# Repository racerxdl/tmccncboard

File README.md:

# tmccncboard

TMC2209 GRBL-ESP32 CNC Board

Made with Kicad 6.0

# FluidNC Configuration

This is the current profile I'm using for [FluidNC](https://github.com/bdring/FluidNC). Its currently WIP and should be used with care.

```yaml
board: Teske's Lab TMC CNC
name: TMCCNC
stepping:
  engine: RMT
  idle_ms: 255
  pulse_us: 2
  dir_delay_us: 1
  disable_delay_us: 0

axes:
  shared_stepper_disable_pin: gpio.27
  x:
    steps_per_mm: 1600.000
    max_rate_mm_per_min: 5000.000
    acceleration_mm_per_sec2: 100.000
    max_travel_mm: 250.000
    soft_limits: false
    homing:
      cycle: 2
      positive_direction: false
      mpos_mm: 150.000
      feed_mm_per_min: 100.000
      seek_mm_per_min: 200.000
      settle_ms: 500
      seek_scaler: 1.100
      feed_scaler: 1.100

    motor0:
      limit_neg_pin: NO_PIN
      limit_pos_pin: NO_PIN
      limit_all_pin: gpio.36
      hard_limits: false
      pulloff_mm:1.000

      tmc_2209:
        uart:
          txd_pin: gpio.17
          rxd_pin: gpio.16
        run_mode: StealthChop
        homing_mode: StallGuard
        step_pin: gpio.2
        direction_pin: gpio.4
        addr: 0
        r_sense_ohms: 0.110
        run_amps: 1.000
        hold_amps: 0.500
        microsteps: 16
  y:
    steps_per_mm: 400.000
    max_rate_mm_per_min: 5000.000
    acceleration_mm_per_sec2: 100.000
    max_travel_mm: 490.000
    soft_limits: false
    homing:
      cycle: 2
      positive_direction: true
      mpos_mm: 150.000
      feed_mm_per_min: 100.000
      seek_mm_per_min: 200.000
      settle_ms: 500
      seek_scaler: 1.100
      feed_scaler: 1.100

    motor0:
      limit_neg_pin: NO_PIN
      limit_pos_pin: NO_PIN
      limit_all_pin: gpio.39
      hard_limits: false
      pulloff_mm:1.000

      tmc_2209:
        run_mode: StealthChop
        homing_mode: StallGuard
        step_pin: gpio.12
        direction_pin: gpio.14
        addr: 1
        r_sense_ohms: 0.110
        run_amps: 1.000
        hold_amps: 0.500
        microsteps: 16

    motor1:
      limit_neg_pin: NO_PIN
      limit_pos_pin: NO_PIN
      limit_all_pin: gpio.34
      hard_limits: false
      pulloff_mm: 1.000
      tmc_2209:
        run_mode: StealthChop
        homing_mode: StallGuard
        step_pin: gpio.33
        direction_pin: gpio.32
        addr: 3
        r_sense_ohms: 0.110
        run_amps: 1.000
        hold_amps: 0.500
        microsteps: 16

  z:
    steps_per_mm: 400.000
    max_rate_mm_per_min: 5000.000
    acceleration_mm_per_sec2: 100.000
    max_travel_mm: 100.000
    soft_limits: false
    homing:
      cycle: 1
      positive_direction: true
      mpos_mm: 150.000
      feed_mm_per_min: 100.000
      seek_mm_per_min: 800.000
      settle_ms: 500
      seek_scaler: 1.100
      feed_scaler: 1.100

    motor0:
      limit_neg_pin: NO_PIN
      limit_pos_pin: NO_PIN
      limit_all_pin: gpio.35
      hard_limits: false
      pulloff_mm:1.000

      tmc_2209:
        run_mode: StealthChop
        homing_mode: StallGuard
        step_pin: gpio.26
        direction_pin: gpio.25
        addr: 2
        r_sense_ohms: 0.110
        run_amps: 1.000
        hold_amps: 0.500
        microsteps: 16

spi:
  miso_pin: gpio.19
  mosi_pin: gpio.23
  sck_pin: gpio.18

sdcard:
  cs_pin: gpio.5
  card_detect_pin: NO_PIN

probe:
  pin: NO_PIN
  check_mode_start: true

start:
  must_home: false

PWM:
  pwm_hz: 5000
  output_pin: gpio.13
  enable_pin: NO_PIN
  direction_pin: NO_PIN
  disable_with_s0: false
  s0_with_disable: true
  spinup_ms: 1000
  spindown_ms: 1000
  tool_num: 0
  speed_map: 0=0.000% 1000=100.000%

```

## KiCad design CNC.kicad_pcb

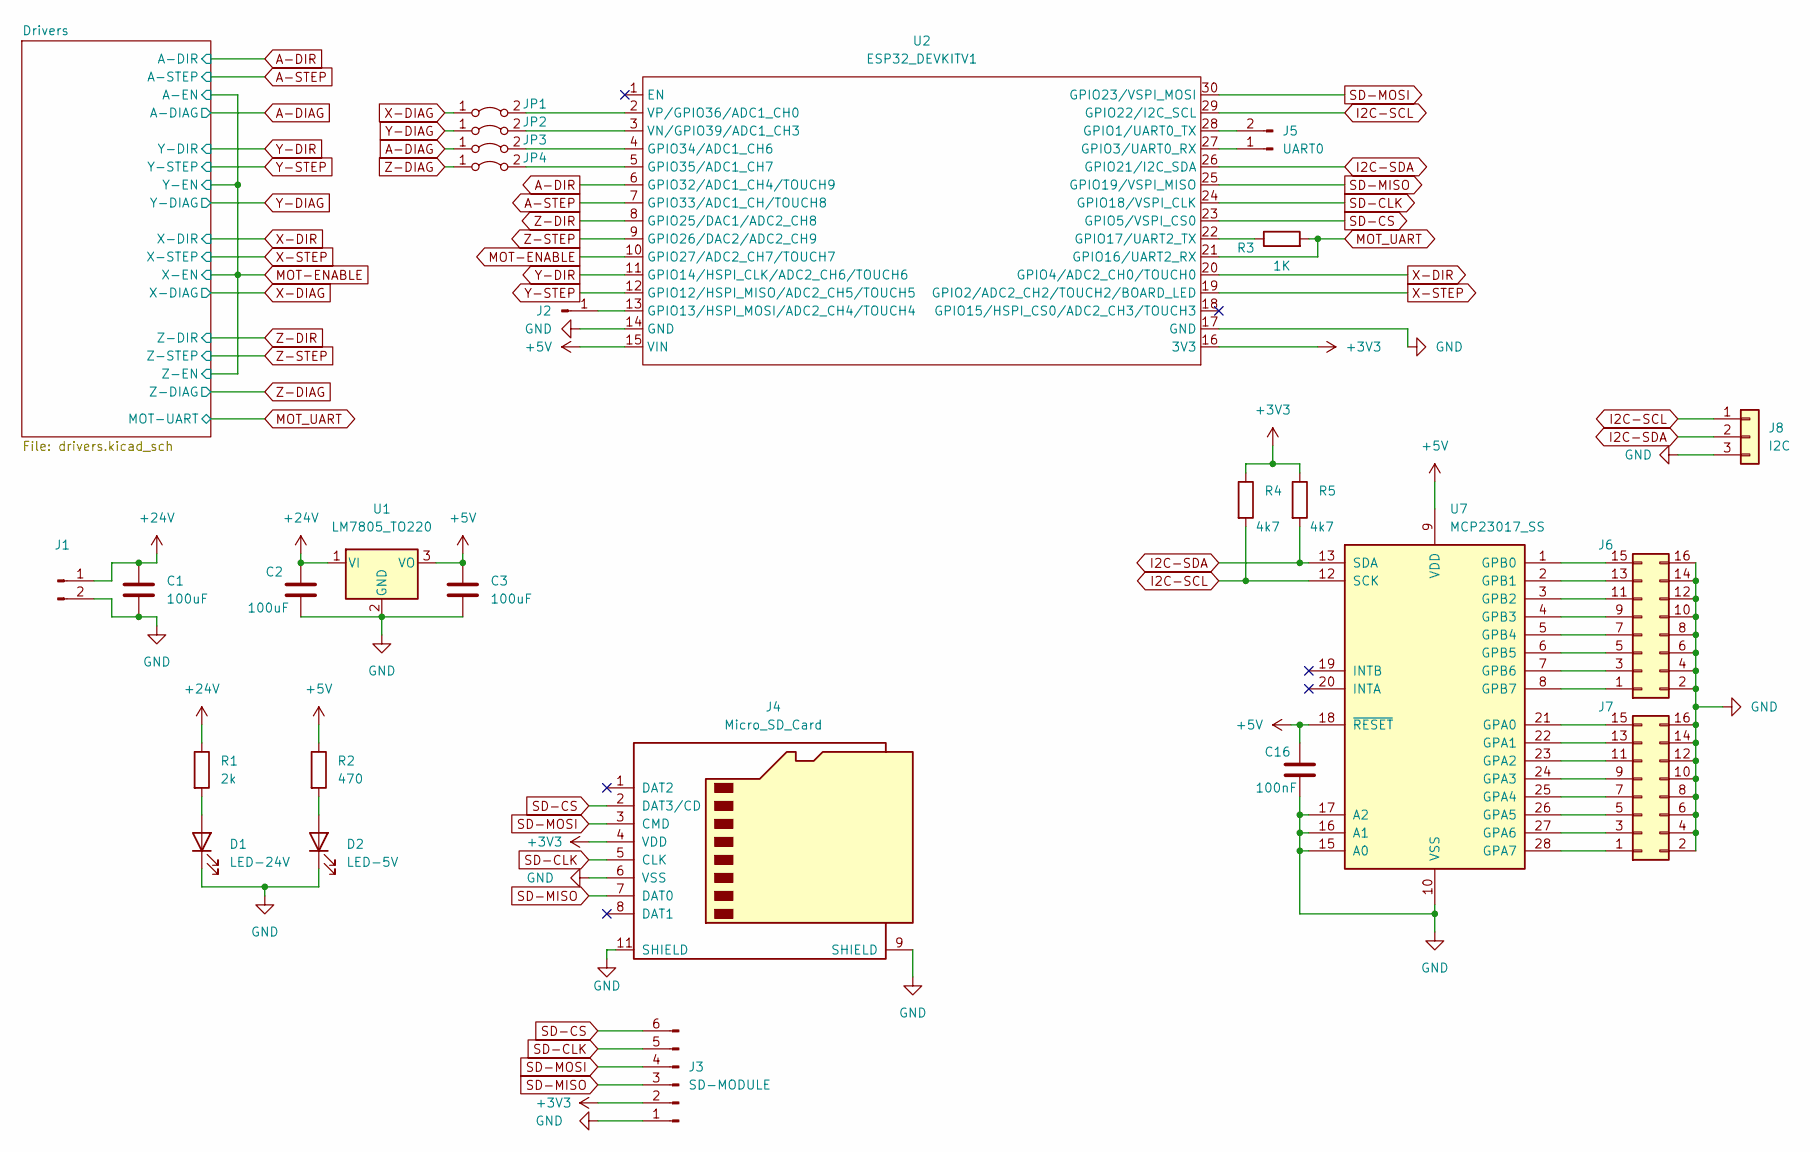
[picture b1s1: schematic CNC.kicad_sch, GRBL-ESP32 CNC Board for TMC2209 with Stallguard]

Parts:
C1, C2, C3: 100uF; CP_Radial_D8.0mm_P3.50mm
C16: 100nF; C_0805_2012Metric_Pad1.18x1.45mm_HandSolder
D1: LED-24V; LED_D5.0mm
D2: LED-5V; LED_D5.0mm
J1: Conn_01x02_Male; Altech_AK300_1x02_P5.00mm_45-Degree
J2: Conn_01x01_Male; PinHeader_1x01_P2.54mm_Vertical
J3: SD-MODULE; PinHeader_1x06_P2.54mm_Horizontal
J4: Micro_SD_Card; microSD_HC_Hirose_DM3AT-SF-PEJM5
J5: UART0; PinHeader_1x02_P2.54mm_Vertical
J6, J7: Conn_02x08_Odd_Even; IDC-Header_2x08_P2.54mm_Vertical
J8: I2C; FanPinHeader_1x03_P2.54mm_Vertical
JP1, JP2, JP3, JP4: Jumper_2_Bridged; PinHeader_1x02_P2.54mm_Vertical
R1: 2k; R_0805_2012Metric_Pad1.20x1.40mm_HandSolder
R2: 470; R_0805_2012Metric_Pad1.20x1.40mm_HandSolder
R3: 1K; R_0805_2012Metric_Pad1.20x1.40mm_HandSolder
R4, R5: 4k7; R_0805_2012Metric_Pad1.20x1.40mm_HandSolder
U1: LM7805_TO220; TO-220-3_Vertical
U2: ESP32_DEVKITV1; ESP32 DEVKITV1
U7: MCP23017_SS; SSOP-28_5.3x10.2mm_P0.65mm

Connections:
+3V3: J3.2, J4.4 (VDD), R4.1, R5.1, U2.16 (3V3); also elsewhere on the board
+5V: C3.1, C16.1, R2.1, U1.3 (VO), U2.15 (VIN), U7.9 (VDD), U7.18 (~RESET)
+24V: C1.1, C2.1, J1.1, R1.1, U1.1 (VI); also elsewhere on the board
A-DIAG: JP3.1 (A); also elsewhere on the board
A-DIR: U2.6 (GPIO32/ADC1_CH4/TOUCH9); also elsewhere on the board
A-STEP: U2.7 (GPIO33/ADC1_CH/TOUCH8); also elsewhere on the board
GND: C1.2, C2.2, C3.2, C16.2, D1.1 (K), D2.1 (K), J1.2, J3.1, J4.6 (VSS), J4.9 (SHIELD), J4.11 (SHIELD), J6.2, J6.4, J6.6, J6.8, J6.10, J6.12, J6.14, J6.16, J7.2, J7.4, J7.6, J7.8, J7.10, J7.12, J7.14, J7.16, J8.3, U1.2 (GND), U2.14 (GND), U2.17 (GND), U7.10 (VSS), U7.15 (A0), U7.16 (A1), U7.17 (A2); also elsewhere on the board
I2C-SCL: J8.1, R4.2, U2.29 (GPIO22/I2C_SCL), U7.12 (SCK)
I2C-SDA: J8.2, R5.2, U2.26 (GPIO21/I2C_SDA), U7.13 (SDA)
MOT-ENABLE: U2.10 (GPIO27/ADC2_CH7/TOUCH7); also elsewhere on the board
MOT_UART: R3.2, U2.21 (GPIO16/UART2_RX); also elsewhere on the board
unnamed: D1.2 (A), R1.2
unnamed: D2.2 (A), R2.2
unnamed: J2.1, U2.13 (GPIO13/HSPI_MOSI/ADC2_CH4/TOUCH4)
unnamed: J5.1, U2.27 (GPIO3/UART0_RX)
unnamed: J5.2, U2.28 (GPIO1/UART0_TX)
unnamed: J6.1, U7.8 (GPB7)
unnamed: J6.3, U7.7 (GPB6)
unnamed: J6.5, U7.6 (GPB5)
unnamed: J6.7, U7.5 (GPB4)
unnamed: J6.9, U7.4 (GPB3)
unnamed: J6.11, U7.3 (GPB2)
unnamed: J6.13, U7.2 (GPB1)
unnamed: J6.15, U7.1 (GPB0)
unnamed: J7.1, U7.28 (GPA7)
unnamed: J7.3, U7.27 (GPA6)
unnamed: J7.5, U7.26 (GPA5)
unnamed: J7.7, U7.25 (GPA4)
unnamed: J7.9, U7.24 (GPA3)
unnamed: J7.11, U7.23 (GPA2)
unnamed: J7.13, U7.22 (GPA1)
unnamed: J7.15, U7.21 (GPA0)
unnamed: JP1.2 (B), U2.2 (VP/GPIO36/ADC1_CH0)
unnamed: JP2.2 (B), U2.3 (VN/GPIO39/ADC1_CH3)
unnamed: JP3.2 (B), U2.4 (GPIO34/ADC1_CH6)
unnamed: JP4.2 (B), U2.5 (GPIO35/ADC1_CH7)
unnamed: R3.1, U2.22 (GPIO17/UART2_TX)
SD-CLK: J3.5, J4.5 (CLK), U2.24 (GPIO18/VSPI_CLK)
SD-CS: J3.6, J4.2 (DAT3/CD), U2.23 (GPIO5/VSPI_CS0)
SD-MISO: J3.3, J4.7 (DAT0), U2.25 (GPIO19/VSPI_MISO)
SD-MOSI: J3.4, J4.3 (CMD), U2.30 (GPIO23/VSPI_MOSI)
X-DIAG: JP1.1 (A); also elsewhere on the board
X-DIR: U2.20 (GPIO4/ADC2_CH0/TOUCH0); also elsewhere on the board
X-STEP: U2.19 (GPIO2/ADC2_CH2/TOUCH2/BOARD_LED); also elsewhere on the board
Y-DIAG: JP2.1 (A); also elsewhere on the board
Y-DIR: U2.11 (GPIO14/HSPI_CLK/ADC2_CH6/TOUCH6); also elsewhere on the board
Y-STEP: U2.12 (GPIO12/HSPI_MISO/ADC2_CH5/TOUCH5); also elsewhere on the board
Z-DIAG: JP4.1 (A); also elsewhere on the board
Z-DIR: U2.8 (GPIO25/DAC1/ADC2_CH8); also elsewhere on the board
Z-STEP: U2.9 (GPIO26/DAC2/ADC2_CH9); also elsewhere on the board

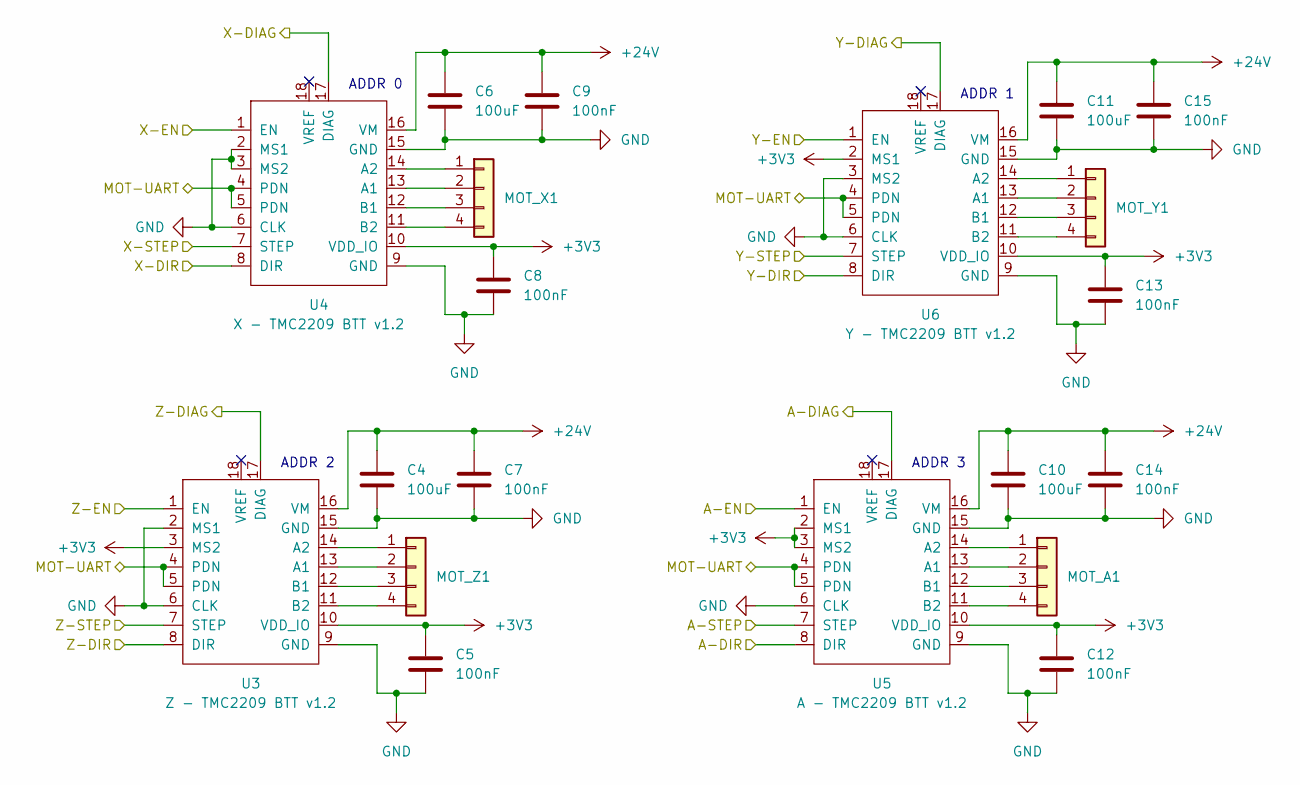
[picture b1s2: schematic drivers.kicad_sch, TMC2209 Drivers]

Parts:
C4, C6, C10, C11: 100uF; CP_Radial_D8.0mm_P3.50mm
C5, C7, C8, C9, C12, C13, C14, C15: 100nF; C_0805_2012Metric_Pad1.18x1.45mm_HandSolder
MOT_A1: Conn_01x04; PinHeader_1x04_P2.54mm_Vertical
MOT_X1: Conn_01x04; PinHeader_1x04_P2.54mm_Vertical
MOT_Y1: Conn_01x04; PinHeader_1x04_P2.54mm_Vertical
MOT_Z1: Conn_01x04; PinHeader_1x04_P2.54mm_Vertical
U3: Z - TMC2209 BTT v1.2; BTT-TMC2209
U4: X - TMC2209 BTT v1.2; BTT-TMC2209
U5: A - TMC2209 BTT v1.2; BTT-TMC2209
U6: Y - TMC2209 BTT v1.2; BTT-TMC2209

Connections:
+3V3: C5.1, C8.1, C12.1, C13.1, U3.3 (MS2), U3.10 (VDD_IO), U4.10 (VDD_IO), U5.2 (MS1), U5.3 (MS2), U5.10 (VDD_IO), U6.2 (MS1), U6.10 (VDD_IO); also elsewhere on the board
+24V: C4.1, C6.1, C7.1, C9.1, C10.1, C11.1, C14.1, C15.1, U3.16 (VM), U4.16 (VM), U5.16 (VM), U6.16 (VM); also elsewhere on the board
A-DIAG: U5.17 (DIAG); also elsewhere on the board
A-DIR: U5.8 (DIR); also elsewhere on the board
A-STEP: U5.7 (STEP); also elsewhere on the board
GND: C4.2, C5.2, C6.2, C7.2, C8.2, C9.2, C10.2, C11.2, C12.2, C13.2, C14.2, C15.2, U3.2 (MS1), U3.6 (CLK), U3.9 (GND), U3.15 (GND), U4.2 (MS1), U4.3 (MS2), U4.6 (CLK), U4.9 (GND), U4.15 (GND), U5.6 (CLK), U5.9 (GND), U5.15 (GND), U6.3 (MS2), U6.6 (CLK), U6.9 (GND), U6.15 (GND); also elsewhere on the board
MOT-ENABLE: U3.1 (EN), U4.1 (EN), U5.1 (EN), U6.1 (EN); also elsewhere on the board
MOT_UART: U3.4 (PDN), U3.5 (PDN), U4.4 (PDN), U4.5 (PDN), U5.4 (PDN), U5.5 (PDN), U6.4 (PDN), U6.5 (PDN); also elsewhere on the board
unnamed: MOT_A1.1, U5.14 (A2)
unnamed: MOT_A1.2, U5.13 (A1)
unnamed: MOT_A1.3, U5.12 (B1)
unnamed: MOT_A1.4, U5.11 (B2)
unnamed: MOT_X1.1, U4.14 (A2)
unnamed: MOT_X1.2, U4.13 (A1)
unnamed: MOT_X1.3, U4.12 (B1)
unnamed: MOT_X1.4, U4.11 (B2)
unnamed: MOT_Y1.1, U6.14 (A2)
unnamed: MOT_Y1.2, U6.13 (A1)
unnamed: MOT_Y1.3, U6.12 (B1)
unnamed: MOT_Y1.4, U6.11 (B2)
unnamed: MOT_Z1.1, U3.14 (A2)
unnamed: MOT_Z1.2, U3.13 (A1)
unnamed: MOT_Z1.3, U3.12 (B1)
unnamed: MOT_Z1.4, U3.11 (B2)
X-DIAG: U4.17 (DIAG); also elsewhere on the board
X-DIR: U4.8 (DIR); also elsewhere on the board
X-STEP: U4.7 (STEP); also elsewhere on the board
Y-DIAG: U6.17 (DIAG); also elsewhere on the board
Y-DIR: U6.8 (DIR); also elsewhere on the board
Y-STEP: U6.7 (STEP); also elsewhere on the board
Z-DIAG: U3.17 (DIAG); also elsewhere on the board
Z-DIR: U3.8 (DIR); also elsewhere on the board
Z-STEP: U3.7 (STEP); also elsewhere on the board

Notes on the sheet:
ADDR 2
ADDR 1
ADDR 3
ADDR 0

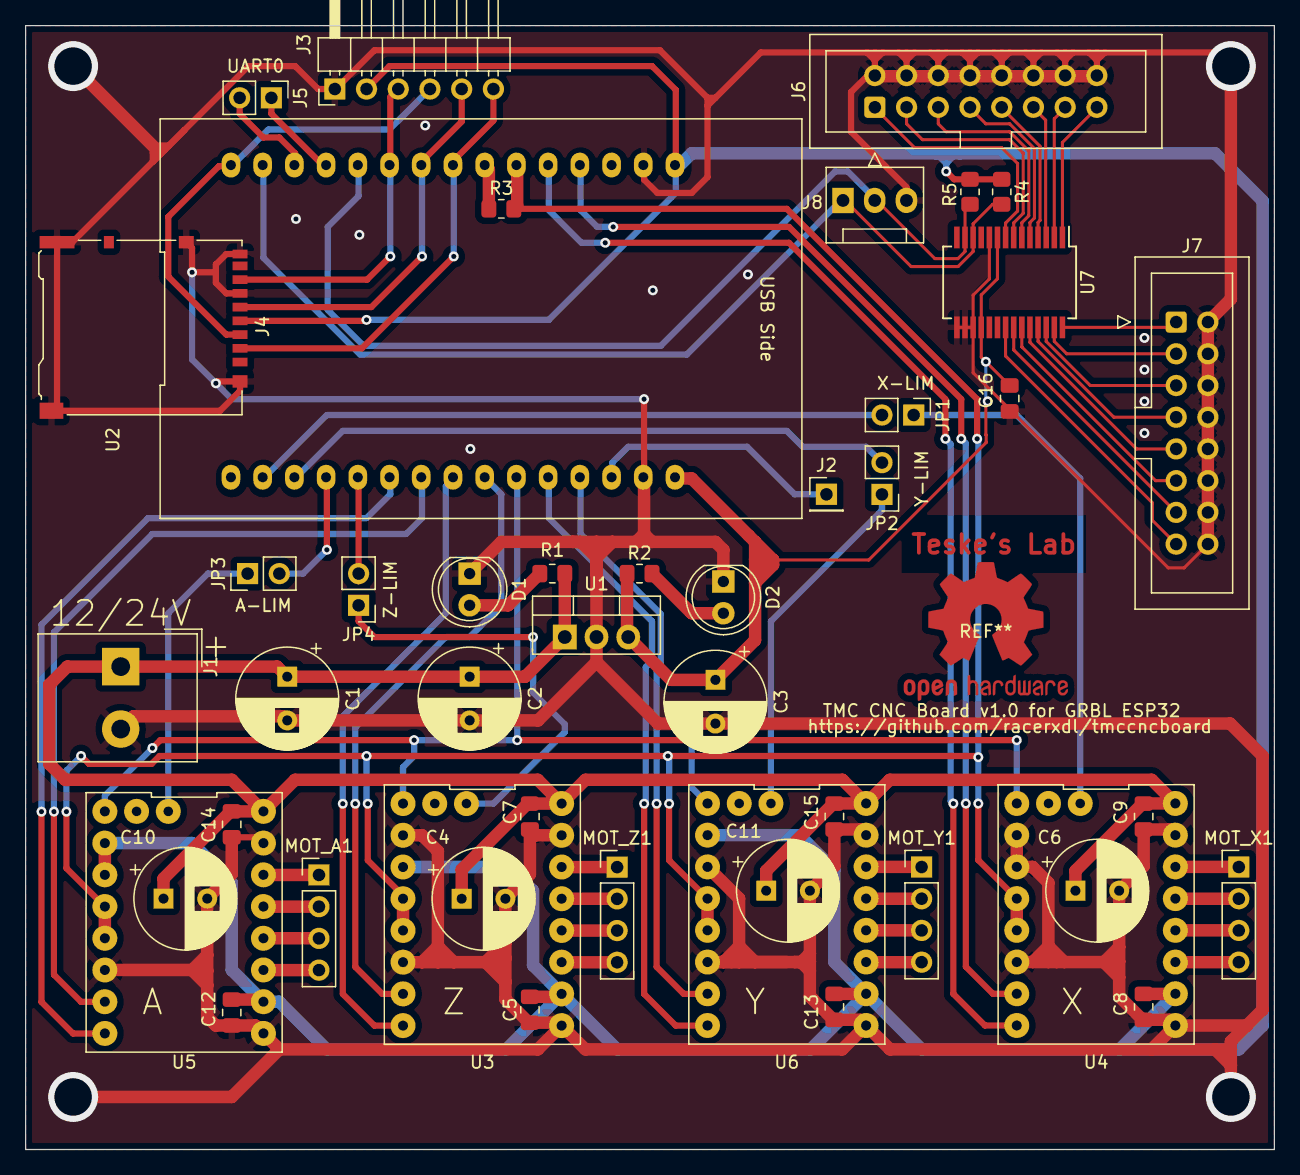
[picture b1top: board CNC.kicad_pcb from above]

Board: 2 copper layers, 100.0 x 90.0 mm, 46 parts (0 on the bottom side), 66 nets.

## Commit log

2022-01-03 Add preliminary gerber files
2022-01-04 Added I/O Expander and fixed DRC
2022-01-25 Fix ESP32-USB direction on PCB
2022-01-29 Add LICENSE
